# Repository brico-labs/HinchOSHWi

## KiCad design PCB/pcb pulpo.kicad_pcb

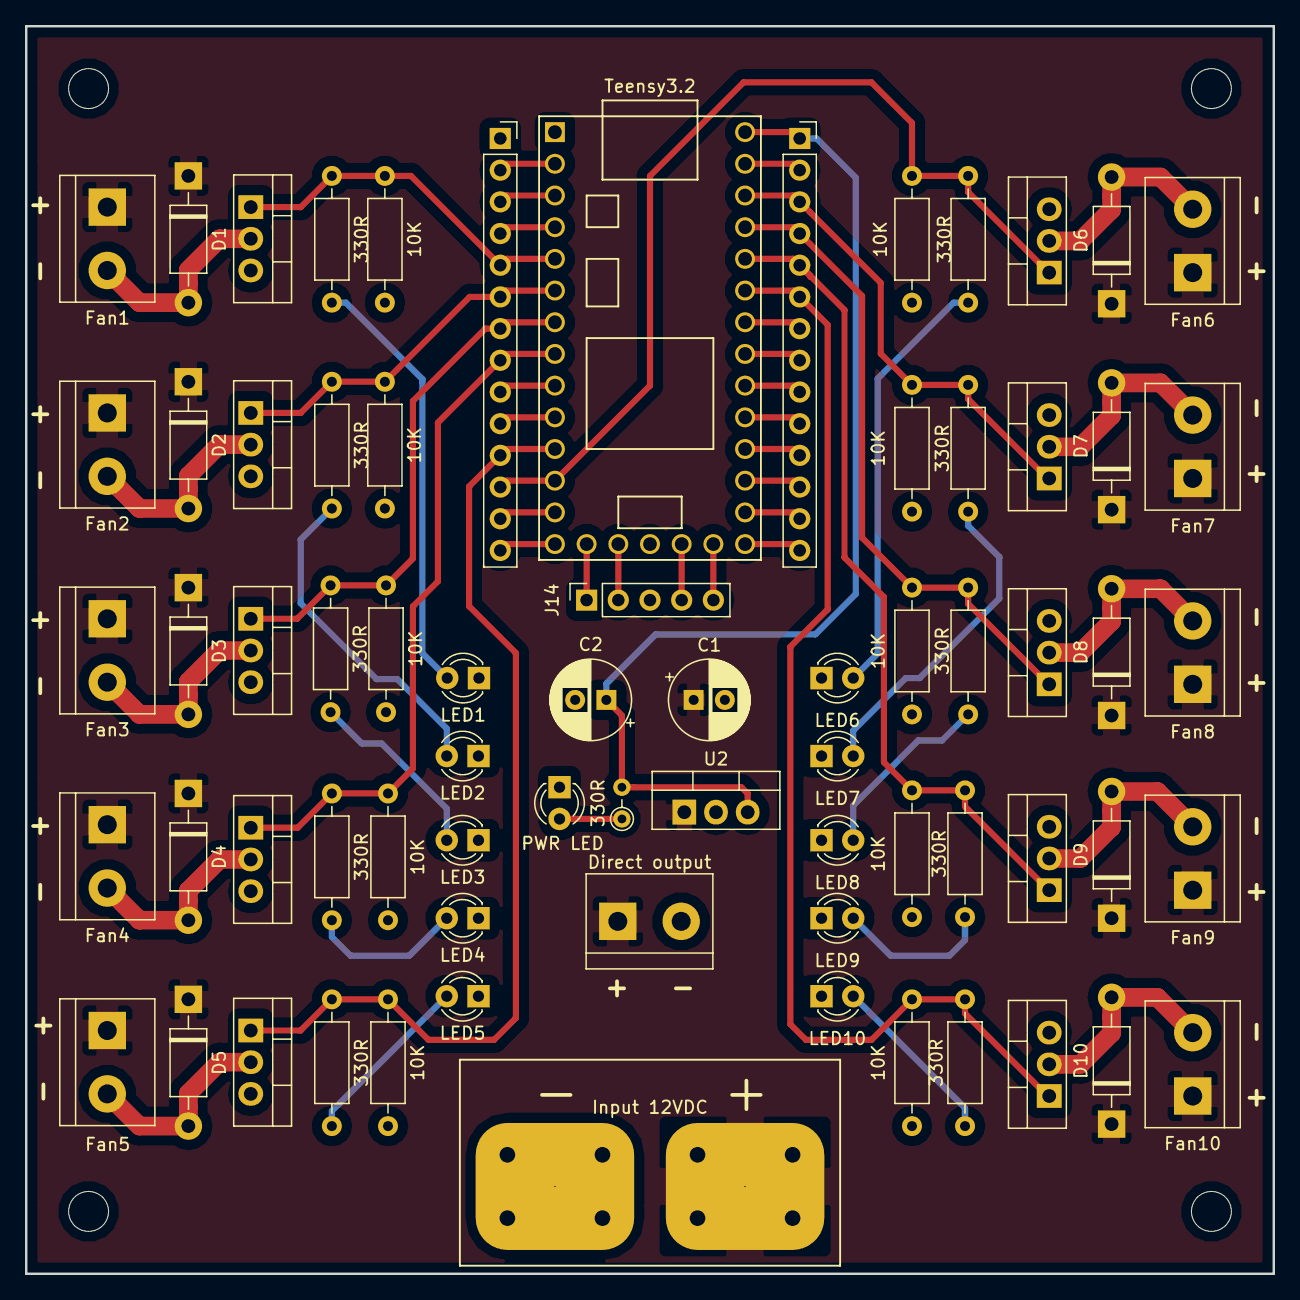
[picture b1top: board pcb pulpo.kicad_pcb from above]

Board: 2 copper layers, 100.0 x 100.0 mm, 71 parts (0 on the bottom side), 54 nets.

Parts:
10K, 10K#2, 10K#3, 10K#4, 10K#5, 10K#6, 10K#7, 10K#8, 10K#9, 10K#10: 10K; R_Axial_DIN0207_L6.3mm_D2.5mm_P10.16mm_Horizontal
330R, 330R#2, 330R#3, 330R#4, 330R#5, 330R#6, 330R#7, 330R#8, 330R#9, 330R#10: 330R; R_Axial_DIN0207_L6.3mm_D2.5mm_P10.16mm_Horizontal
330R#11: R_Small; R_Axial_DIN0204_L3.6mm_D1.6mm_P2.54mm_Vertical
C1, C2: CP; CP_Radial_D6.3mm_P2.50mm
D1, D2, D3, D4, D5, D6, D7, D8, D9, D10: 1N4004; D_DO-41_SOD81_P10.16mm_Horizontal
Direct output: Direct output; TerminalBlock_bornier-2_P5.08mm
Input 12VDC: Entrada 12V; conector pablo pulpo hinchoshwi
J1: Fan1; TerminalBlock_bornier-2_P5.08mm
J2: Fan2; TerminalBlock_bornier-2_P5.08mm
J3: Fan3; TerminalBlock_bornier-2_P5.08mm
J4: Fan4; TerminalBlock_bornier-2_P5.08mm
J5: Fan5; TerminalBlock_bornier-2_P5.08mm
J6: Fan6; TerminalBlock_bornier-2_P5.08mm
J7: Fan7; TerminalBlock_bornier-2_P5.08mm
J8: Fan8; TerminalBlock_bornier-2_P5.08mm
J9: Fan9; TerminalBlock_bornier-2_P5.08mm
J10: Fan10; TerminalBlock_bornier-2_P5.08mm
J12: izq; PinSocket_1x14_P2.54mm_Vertical
J13: dcha; PinSocket_1x14_P2.54mm_Vertical
J14: inf; PinSocket_1x05_P2.54mm_Vertical
LED1, LED2, LED3, LED4, LED5, LED6, LED7, LED8, LED9, LED10: LED; LED_D3.0mm
MOS_1, MOS_2, MOS_3, MOS_4, MOS_5, MOS_6, MOS_7, MOS_8, MOS_9, MOS_10: RFP50N06; TO-220-3_Vertical
PWR LED: LED; LED_D3.0mm
U1: Teensy3.2; Teensy30_31_32_LC
U2: LM7805_TO220; TO-220-3_Vertical

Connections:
+12V: C1.1, D1.1, D2.1, D3.1, D4.1, D5.1, D6.1, D7.1, D8.1, D9.1, D10.1, Direct output.1, Input 12VDC.1, J1.1, J2.1, J3.1, J4.1, J5.1, J6.1, J7.1, J8.1, J9.1, J10.1, U2.1
GND: 10K.2, 10K#2.2, 10K#3.2, 10K#4.2, 10K#5.2, 10K#6.2, 10K#7.2, 10K#8.2, 10K#9.2, 10K#10.2, C1.2, C2.2, Direct output.2, Input 12VDC.2, J12.1, J14.3, LED1.1, LED2.1, LED3.1, LED4.1, LED5.1, LED6.1, LED7.1, LED8.1, LED9.1, LED10.1, MOS_1.3, MOS_2.3, MOS_3.3, MOS_4.3, MOS_5.3, MOS_6.3, MOS_7.3, MOS_8.3, MOS_9.3, MOS_10.3, PWR LED.1, U1.1, U1.17, U2.2
unnamed: 330R#11.2, C2.1, J13.1, U1.33, U2.3
unnamed: D1.2, J1.2, MOS_1.2
unnamed: D2.2, J2.2, MOS_2.2
unnamed: D3.2, J3.2, MOS_3.2
unnamed: D4.2, J4.2, MOS_4.2
unnamed: D5.2, J5.2, MOS_5.2
unnamed: D6.2, J6.2, MOS_6.2
unnamed: D7.2, J7.2, MOS_7.2
unnamed: D8.2, J8.2, MOS_8.2
unnamed: D9.2, J9.2, MOS_9.2
unnamed: D10.2, J10.2, MOS_10.2
unnamed: J12.2, U1.2
unnamed: J12.3, U1.3
unnamed: J12.4, U1.4
unnamed: J12.9, U1.9
unnamed: J12.10, U1.10
unnamed: J12.13, U1.13
unnamed: J12.14, U1.14
unnamed: J13.2, U1.32
unnamed: J13.7, U1.27
unnamed: J13.8, U1.26
unnamed: J13.9, U1.25
unnamed: J13.10, U1.24
unnamed: J13.11, U1.23
unnamed: J13.12, U1.22
unnamed: J13.13, U1.21
unnamed: J13.14, U1.20
unnamed: J14.1, U1.15
unnamed: J14.2, U1.16
unnamed: J14.4, U1.18
unnamed: J14.5, U1.19
unnamed: 330R.2, LED1.2
unnamed: 330R#2.2, LED2.2
unnamed: 330R#3.2, LED3.2
unnamed: 330R#4.2, LED4.2
unnamed: 330R#5.2, LED5.2
unnamed: 330R#6.2, LED6.2
unnamed: 330R#7.2, LED7.2
unnamed: 330R#8.2, LED8.2
unnamed: 330R#9.2, LED9.2
unnamed: 330R#10.2, LED10.2
unnamed: 330R#11.1, PWR LED.2
pin1: 10K.1, 330R.1, J12.5, MOS_1.1, U1.5
pin2: 10K#2.1, 330R#2.1, J12.6, MOS_2.1, U1.6
pin3: 10K#3.1, 330R#3.1, J12.7, MOS_3.1, U1.7
pin4: 10K#4.1, 330R#4.1, J12.8, MOS_4.1, U1.8
pin5: 10K#5.1, 330R#5.1, J12.11, MOS_5.1, U1.11
pin6: 10K#6.1, 330R#6.1, J12.12, MOS_6.1, U1.12
pin7: 10K#10.1, 330R#10.1, J13.6, MOS_10.1, U1.28
pin8: 10K#9.1, 330R#9.1, J13.5, MOS_9.1, U1.29
pin9: 10K#8.1, 330R#8.1, J13.4, MOS_8.1, U1.30
pin10: 10K#7.1, 330R#7.1, J13.3, MOS_7.1, U1.31

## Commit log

2018-10-22 1st HinchOSHWi commit
2018-10-22 Boceto PCB
2018-10-24 placa terminada
2018-11-07 STLs de ojos. A ver si funcionan
2018-11-10 Añadido código
2018-11-30 añadidos leds a la placa y junta para la cabeza
2018-12-01 Cambio posición LEDs a antes del MOSFET y revisión de estilo en el esquema
2018-12-09 mejoras en componentes
2018-12-17 cambios en la pcb. añadido footprint conector Pablo. Falta cambiar algunos componentes y routear
2018-12-29 Esquema y PCB en versión release 1
2019-01-18 Se añade logo de BricoLabs
2019-03-30 Cambios en la asignación de pines
